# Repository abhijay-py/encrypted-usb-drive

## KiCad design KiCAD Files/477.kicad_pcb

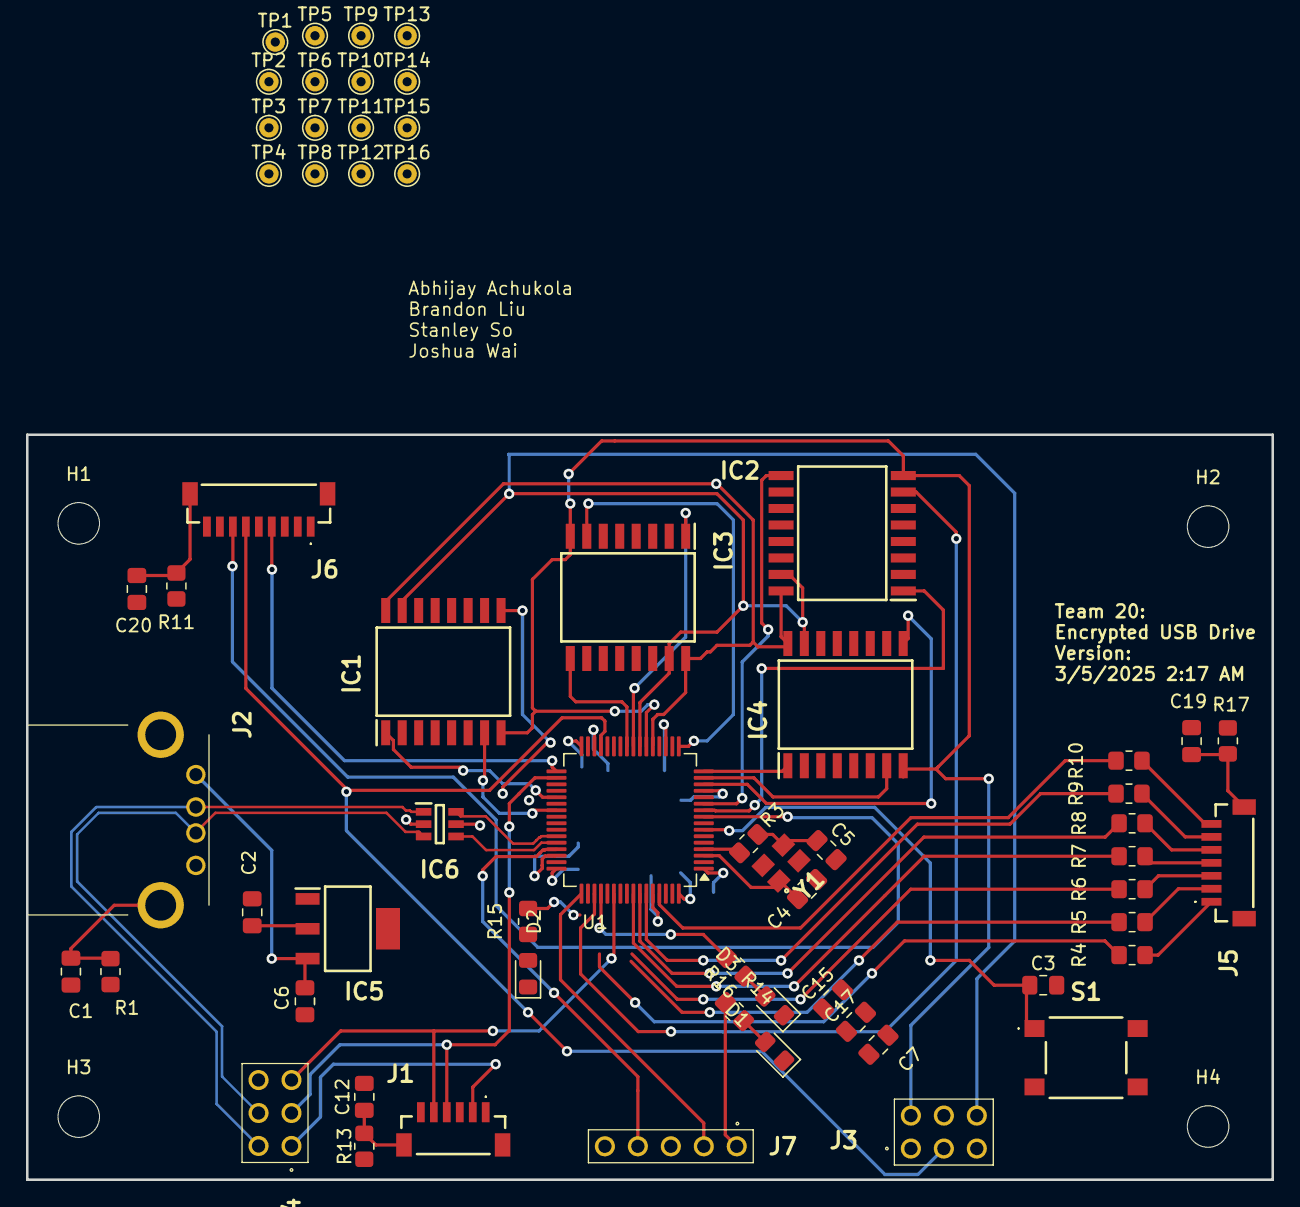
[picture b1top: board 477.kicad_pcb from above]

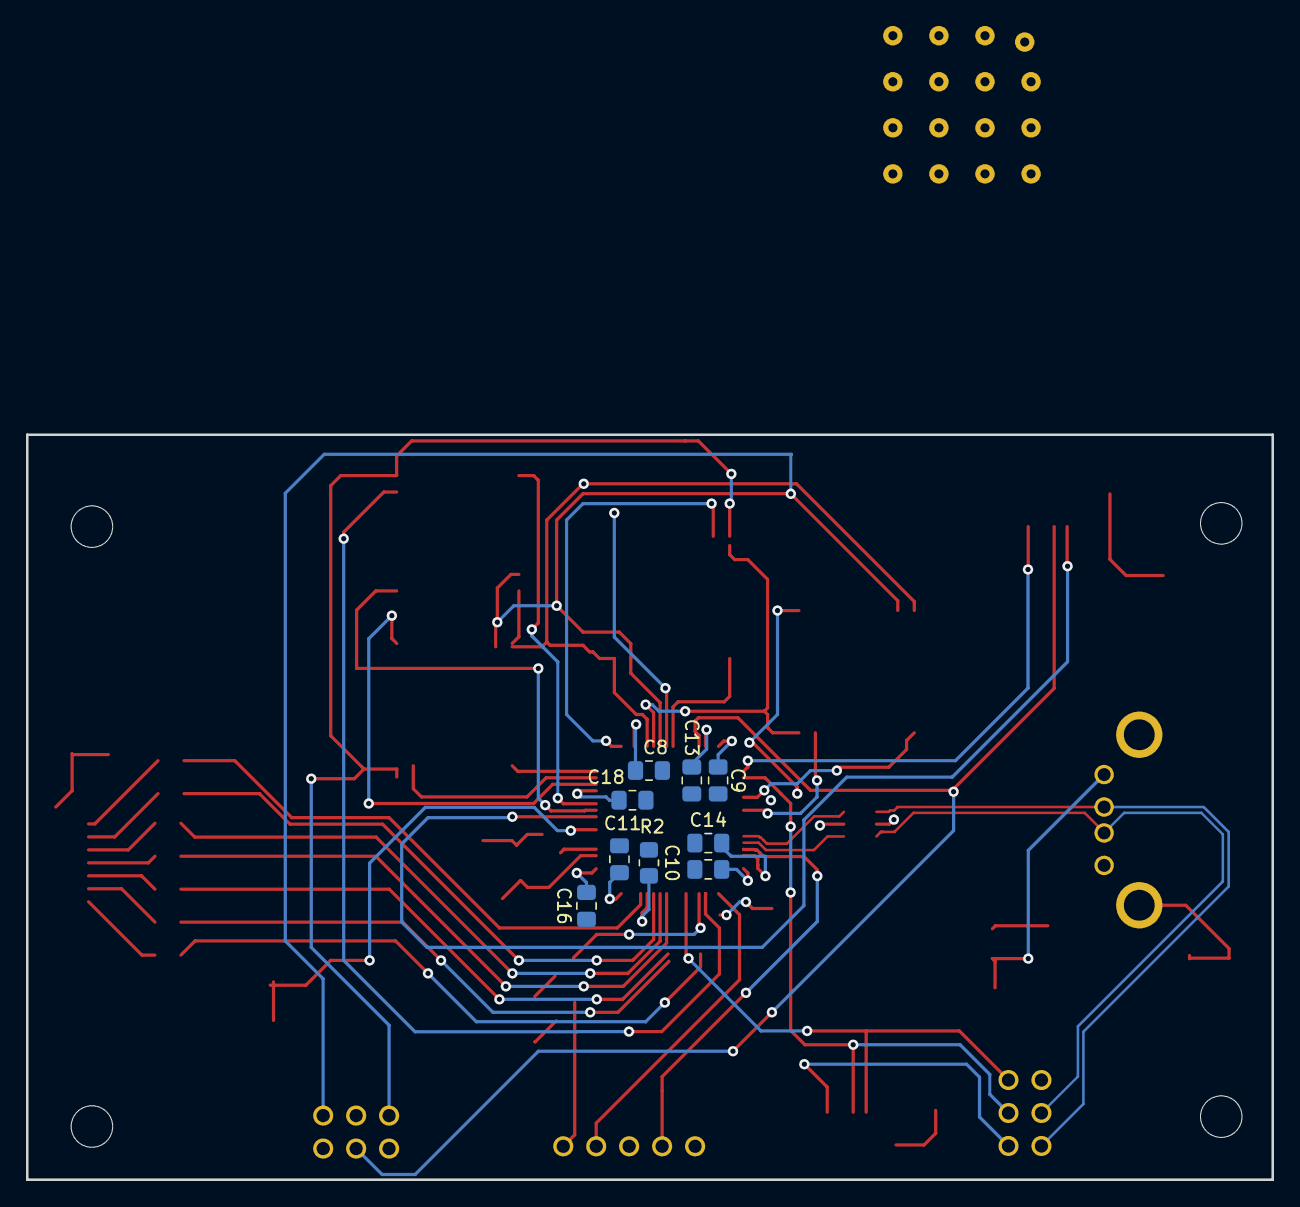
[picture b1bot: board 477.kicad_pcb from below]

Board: 2 copper layers, 96.0 x 57.4 mm, 75 parts (9 on the bottom side), 60 nets.

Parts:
C1, C12, C19, C20: 2.2n; C_0805_2012Metric_Pad1.18x1.45mm_HandSolder
C2: 22u; C_0805_2012Metric_Pad1.18x1.45mm_HandSolder
C3: 0.1u; C_0805_2012Metric_Pad1.18x1.45mm_HandSolder
C4, C5: 10p; C_0805_2012Metric_Pad1.18x1.45mm_HandSolder
C6: 10u; C_0805_2012Metric_Pad1.18x1.45mm_HandSolder
C7: 4.7u; C_0805_2012Metric_Pad1.18x1.45mm_HandSolder
C8, C9, C10, C11, C13, C14, C16, C18: 100n; C_0805_2012Metric_Pad1.18x1.45mm_HandSolder
C15, C17: 1u; C_0805_2012Metric_Pad1.18x1.45mm_HandSolder
D1, D2, D3: LED; LED_0805_2012Metric_Pad1.15x1.40mm_HandSolder
H1, H2, H3, H4: MountingHole; MountingHole_3.2mm_M3_DIN965
IC1, IC2, IC3, IC4: W25N01GVSFIG; SOIC127P1032X264-16N
IC5: AZ1117IH-3.3TRG1; SOT230P700X180-4N
IC6: USBLC6-2SC6; SOT95P280X145-6N
J1: BM06B-SRSS-TBT_LF__SN_; BM06BSRSSTBTLFSN
J2: 6364372-2; 63643722
J3, J4: TSW-103-14-S-D; custom1
J5: BM07B-SRSS-TB_LF__SN_; BM07BSRSSTBLFSN
J6: BM09B-SRSS-TB_LF__SN_; BM09BSRSSTBLFSN
J7: TSW-105-05-F-S; TSW-105-XX-YY-S
R1, R11, R13, R17: 1M; R_0805_2012Metric_Pad1.20x1.40mm_HandSolder
R2: 10k; R_0805_2012Metric_Pad1.20x1.40mm_HandSolder
R3: 330; R_0805_2012Metric_Pad1.20x1.40mm_HandSolder
R4, R5, R6, R7, R8, R9, R10: 1k; R_0805_2012Metric_Pad1.20x1.40mm_HandSolder
R14, R15, R16: 220; R_0805_2012Metric_Pad1.20x1.40mm_HandSolder
S1: 222AMVBAR; custom
TP1, TP2, TP3, TP4, TP5, TP6, TP7, TP8, TP9, TP10, TP11, TP12, TP13, TP14, TP15, TP16: TestPoint; TestPoint_THTPad_D1.5mm_Drill0.7mm
U1: STM32H7A3RGTx; LQFP-64_10x10mm_P0.5mm
Y1: ABM8G-48.000MHZ-18-D2Y-T; ABM8G

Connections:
+5V: C6.1, IC5.3 (INPUT), IC6.5 (VBUS), J2.1, J6.3, J6.9
D+: IC6.3 (I/O2_1), J2.3, J4.4
D-: IC6.1 (I/O1_1), J2.2, J4.2
GND: C1.2, C2.2, C3.2, C4.2, C5.2, C6.2, C7.2, C8.2, C9.2, C10.2, C11.2, C12.2, C13.2, C14.2, C15.2, C16.2, C17.2, C18.2, C19.2, C20.2, D1.1 (K), D2.1 (K), D3.1 (K), IC1.10 (GND), IC2.10 (GND), IC3.10 (GND), IC4.10 (GND), IC5.1 (ADJ/GND), IC6.2 (GND), J2.4, J3.1, J4.6, J6.1, J6.2, J6.8, J7.3, R1.2, R2.2, R11.2, R13.2, R17.2, S1.2 (NO_1), S1.4 (NO_2), U1.12 (VSSA), U1.18 (VSS), U1.31 (VSS), U1.47 (VSS), U1.63 (VSS), Y1.2 (GND_1), Y1.4 (GND_2)
unnamed: C1.1, J2.MH2, R1.1
unnamed: C12.1, J1.MP2, R13.1
unnamed: C19.1, J5.MP2, R17.1
unnamed: C20.1, J6.MP2, R11.1
unnamed: D1.2 (A), R14.1
unnamed: D2.2 (A), R15.1
unnamed: D3.2 (A), R16.1
unnamed: J5.1, R4.1
unnamed: J5.2, R5.1
unnamed: J5.3, R6.1
unnamed: J5.4, R7.2
unnamed: J5.5, R8.2
unnamed: J5.6, R9.1
unnamed: J5.7, R10.2
unnamed: R2.1, U1.60 (BOOT0)
unnamed: C5.1, R3.1, Y1.3 (XTAL_2)
PA0/WP4: IC4.9 (/WP_(IO2_)), U1.14 (PA0)
PA1/CS4: IC4.7 (/CS), U1.15 (PA1)
PA2/HOLD4: IC4.1 (/HOLD_(IO3)), U1.16 (PA2)
PA3/CS3: IC3.7 (/CS), U1.17 (PA3)
PA5/SCK: IC1.16 (CLK), IC2.16 (CLK), IC3.16 (CLK), IC4.16 (CLK), J3.4, U1.21 (PA5)
PA6/MISO: IC1.8 (DO_(IO1_)), IC2.8 (DO_(IO1_)), IC3.8 (DO_(IO1_)), IC4.8 (DO_(IO1_)), J3.2, U1.22 (PA6)
PA7/MOSI: IC1.15 (DI_(IO0_)), IC2.15 (DI_(IO0_)), IC3.15 (DI_(IO0_)), IC4.15 (DI_(IO0_)), J3.6, U1.23 (PA7)
PA9/Debug: R15.2, U1.41 (PA9)
PA13/SWDIO: J7.4, U1.45 (PA13)
PA14/SWCLK: J7.2, U1.49 (PA14)
PB0/KeyR1: R4.2, U1.26 (PB0)
PB1/KeyR2: R5.2, U1.27 (PB1)
PB2/KeyR3: R6.2, U1.28 (PB2)
PB5/KeyR4: R7.1, U1.57 (PB5)
PB6/KeyC1: R8.1, TP16.1, U1.58 (PB6)
PB7/KeyC2: R9.2, TP15.1, U1.59 (PB7)
PB8/KeyC3: R10.1, TP14.1, U1.61 (PB8)
PB10/LCD SCK: J3.3, J6.6, U1.29 (PB10)
PB12/LCD NSS: J6.4, TP13.1, U1.33 (PB12)
PB13/FP TX: J1.4, J4.3, U1.34 (PB13)
PC0/Touch Out: J1.2, J4.1, U1.8 (PC0)
PC1/LCD MOSI: J3.5, J6.7, U1.9 (PC1)
PC2/HOLD2: IC2.1 (/HOLD_(IO3)), U1.10 (PC2)
PC3/WP2: IC2.9 (/WP_(IO2_)), TP2.1, U1.11 (PC3)
PC4/HOLD3: IC3.1 (/HOLD_(IO3)), U1.24 (PC4)
PC5/WP3: IC3.9 (/WP_(IO2_)), U1.25 (PC5)
PC6/HOLD1: IC1.1 (/HOLD_(IO3)), TP5.1, U1.37 (PC6)
PC7/WP1: IC1.9 (/WP_(IO2_)), U1.38 (PC7)
PC9/CS1: IC1.7 (/CS), U1.39 (PC9)
PC10/CS2: IC2.7 (/CS), U1.51 (PC10)
PC11/Debug: R16.2, U1.52 (PC11)
PC14/OSC IN: C4.1, U1.3 (PC14), Y1.1 (XTAL_1)
PC15/OSC OUT: R3.2, U1.4 (PC15)
PD2/FP RX: J1.5, J4.5, U1.54 (PD2)
USB+: IC6.4 (I/O2_2), U1.44 (PA12)
USB-: IC6.6 (I/O1_2), U1.43 (PA11)
VBAT: C2.1, C7.1, C8.1, C9.1, C10.1, C11.1, C15.1, C16.1, C17.1, C18.1, IC1.2 (VCC), IC2.2 (VCC), IC3.2 (VCC), IC4.2 (VCC), IC5.2 (OUTPUT), IC5.4 (VOUT), J1.1, J1.3, J1.6, J7.1, R14.2, U1.1 (VBAT), U1.13 (VDDA), U1.19 (VDD), U1.32 (VDD), U1.48 (VDD), U1.64 (VDD)
VCAP1: C13.1, U1.30 (VCAP)
VCAP2: C14.1, U1.46 (VCAP)
nRST: C3.1, J7.5, S1.1 (COM_1), U1.7 (NRST)

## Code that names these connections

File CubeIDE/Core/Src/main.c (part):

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  GPIO_InitStruct.Pull = GPIO_NOPULL;
  HAL_GPIO_Init(USER_Btn_GPIO_Port, &GPIO_InitStruct);

  /*Configure GPIO pin : PA3 */
  GPIO_InitStruct.Pin = GPIO_PIN_3;
  GPIO_InitStruct.Mode = GPIO_MODE_OUTPUT_PP;
  GPIO_InitStruct.Pull = GPIO_NOPULL;
  GPIO_InitStruct.Speed = GPIO_SPEED_FREQ_LOW;
  HAL_GPIO_Init(GPIOA, &GPIO_InitStruct);

  /*Configure GPIO pins : PB0 PB1 PB2 LD3_Pin
                           PB3 LD2_Pin */
  GPIO_InitStruct.Pin = GPIO_PIN_0|GPIO_PIN_1|GPIO_PIN_2|LD3_Pin
                          |GPIO_PIN_3|LD2_Pin;
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  GPIO_InitStruct.Pull = GPIO_NOPULL;
  HAL_GPIO_Init(USB_OverCurrent_GPIO_Port, &GPIO_InitStruct);

  /*Configure GPIO pins : PB4 PB5 PB6 */
  GPIO_InitStruct.Pin = GPIO_PIN_4|GPIO_PIN_5|GPIO_PIN_6;
  GPIO_InitStruct.Mode = GPIO_MODE_INPUT;
  GPIO_InitStruct.Pull = GPIO_PULLDOWN;
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
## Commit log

2025-03-05 additional usb files added
2025-03-05 additional
2025-03-05 more
2025-03-06 added pcb routing for debug pins
2025-03-06 routed resistors, caps, leds
2025-03-25 cleaned up code with structs, hex values, and constants in header file
2025-03-27 master can read slave data in buffer variable when using debugger

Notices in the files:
CubeIDE/Core/Src/main.c:
Copyright (c) 2025 STMicroelectronics.
All rights reserved.
This software is licensed under terms that can be found in the LICENSE file
